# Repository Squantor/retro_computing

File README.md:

# Various retrocomputing projects
This is a collection of retrocomputing projects.
## Structure
* Hardware contains the schematics and PCB's used by the project
* Software contains the software needed for the project, either embedded or PC side software
* CAD contains drawings of casing/mechanisms etc
## Checking out
This project makes extensive use of submodules, use ```git clone --recurse-submodules https://github.com/Squantor/retro_computing.git``` to clone the repository and its submodules in one go.

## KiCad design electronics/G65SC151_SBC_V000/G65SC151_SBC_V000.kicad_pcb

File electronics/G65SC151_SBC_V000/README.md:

# G65SC151 Single Board Computer Version 0
This is a simple test board for the G65SC151 microcontroller chip. Goal is to bring up this chip and getting to know how to program it. Why? I have some retrocomputing projects planned, and I wanted to learn to program the 6502 processor. Instead of going for the standard 6502 with a RAM, ROM and ACIA/UART chip. The G65SC151 has a few facilities built in:
* 64 bytes of RAM
* 27 GPIO pins
* Interval timer
* Some modem communications block
* 6502 style bus interface
This makes it possible to make a working 6502 system with just adding a ROM chip. Neat!
# HSI (Hardware Software Interface)
Still TODO as schematic is still in progress.
## TODO's
Still some things need to be done:
* schematic entry 
* PCB layout
* Review with one night in between
* Produce
* Assemble
* Test & characterise
* update Readme.md with pictures and BOM
## BOM
The G65SC151 is a long obsolete microcontroller using the 6502 processor architecture. Replicating this project you will have to try your luck with a ebay/aliexpress.

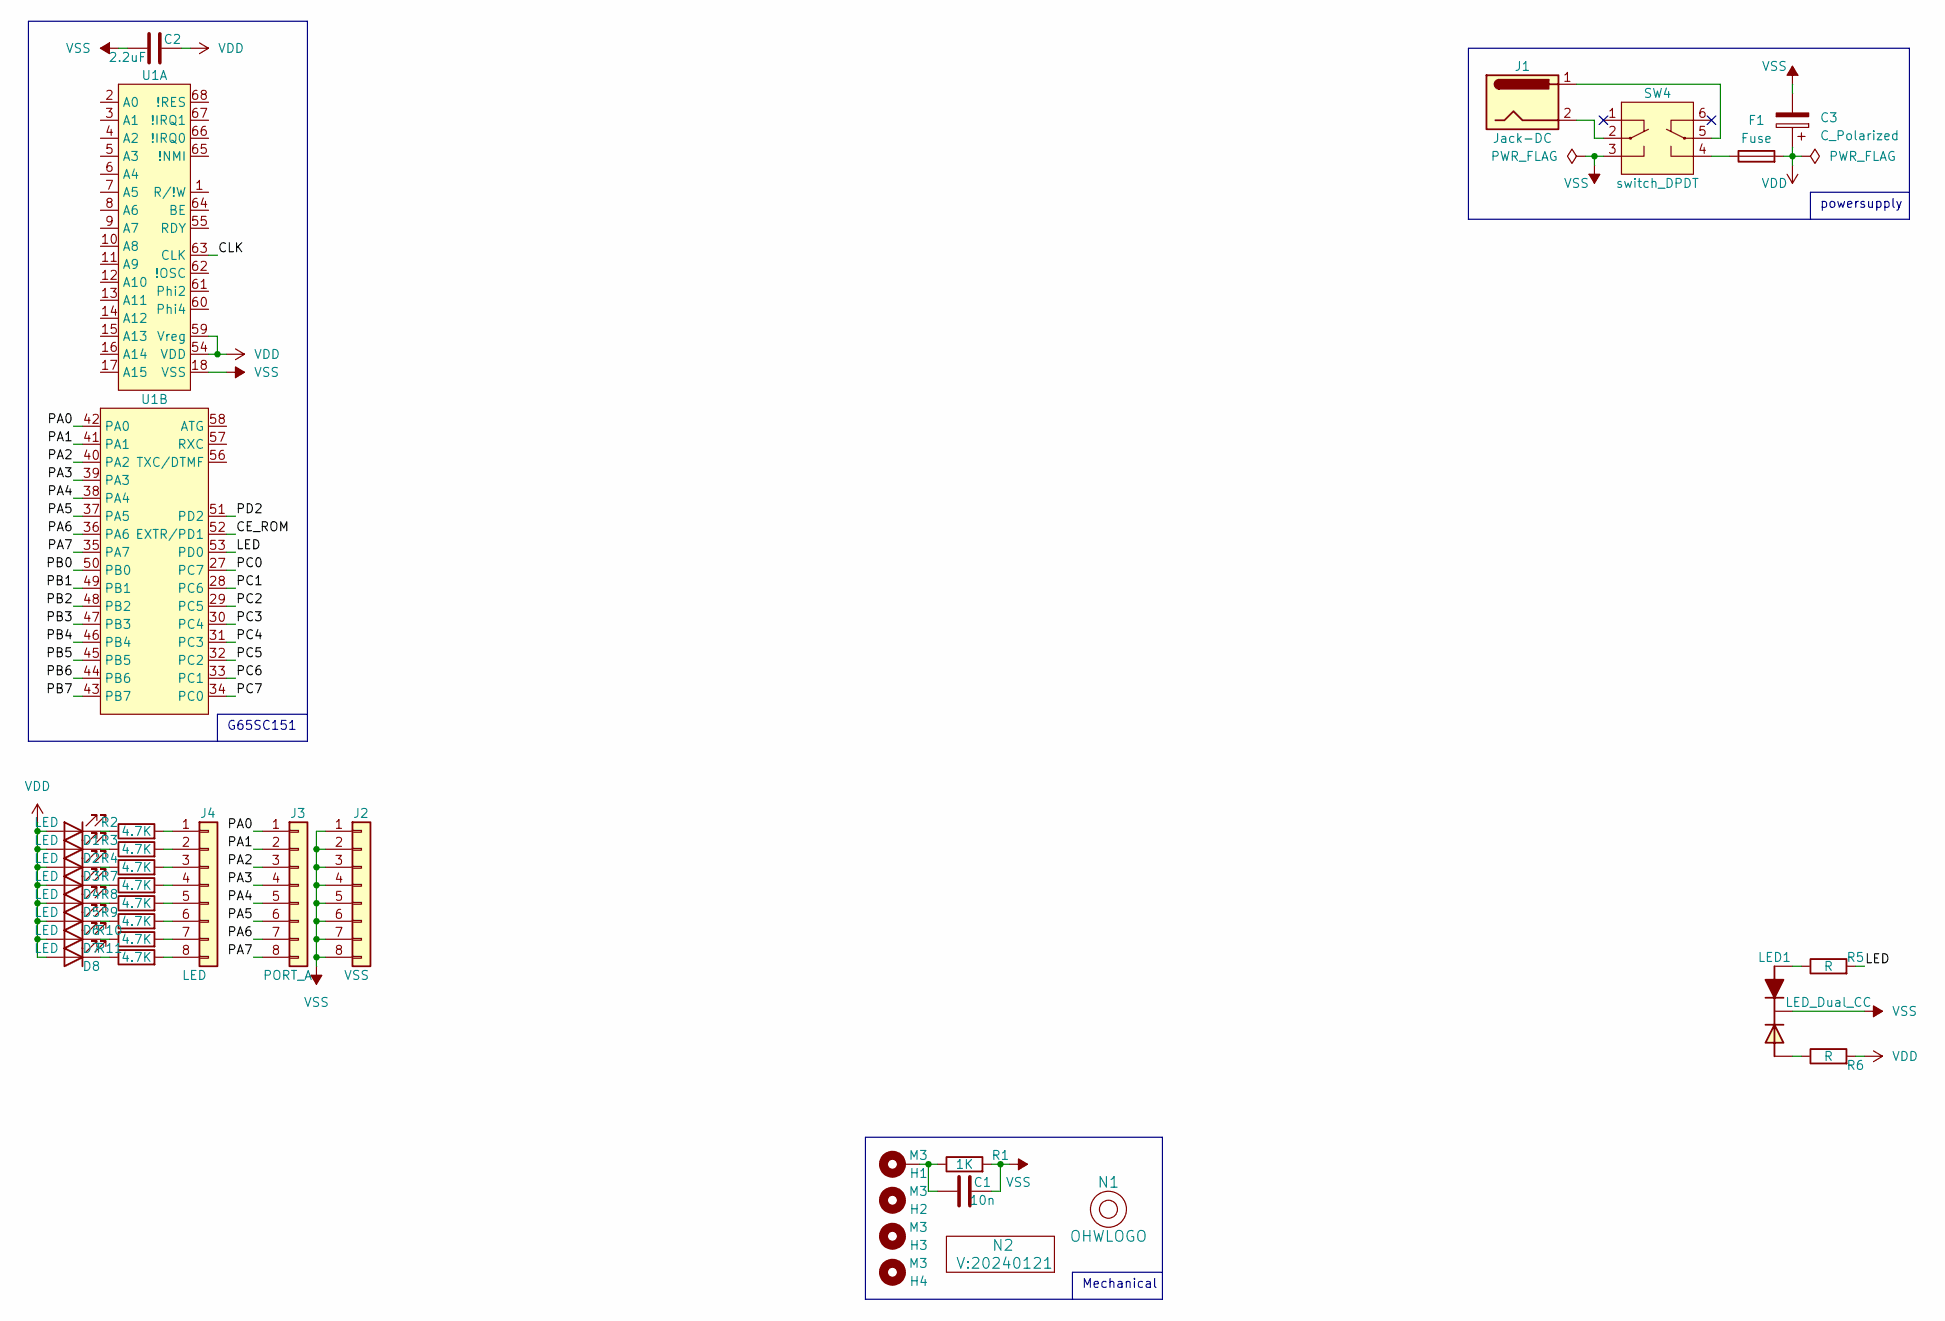
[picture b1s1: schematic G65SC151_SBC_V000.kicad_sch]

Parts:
C1: 10n; C_0805+0603
C2: 2.2uF; C_0805+0603
C3: C_Polarized; C-050-100-elco
D1, D2, D3, D4, D5, D6, D7, D8: LED; LED_0603_hand
F1: Fuse; Fuse_BelFuse_0ZRE0012FF_L8.3mm_W3.8mm
H1, H2, H3, H4: M3; MountingHole_3.2mm_M3_Pad_Via
J1: Jack-DC; BarrelJack_Horizontal_Holed
J2: VSS; Header-0254-1X08-H010
J3: PORT_A; Header-0254-1X08-H010
J4: LED; Header-0254-1X08-H010
LED1: LED_Dual_CC; LED_DUAL_TH245_90deg
N1: OHWLOGO; OSHW-Symbol_6.7x6mm_SilkScreen
N2: V:20240121; Label_Generic
R1: 1K; R_0805+0603
R2, R3, R4, R7, R8, R9, R10, R11: 4.7K; R_0603_hand
R5, R6: R; R_0603_hand
SW4: switch_DPDT; PS-22F02
U1: PLCC-68_THT-Socket

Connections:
/CE_ROM: U1.52 (EXTR/PD1)
/CLK: U1.63 (CLK)
/LED: R5.2, U1.53 (PD0)
/PA0: J3.1, U1.42 (PA0)
/PA1: J3.2, U1.41 (PA1)
/PA2: J3.3, U1.40 (PA2)
/PA3: J3.4, U1.39 (PA3)
/PA4: J3.5, U1.38 (PA4)
/PA5: J3.6, U1.37 (PA5)
/PA6: J3.7, U1.36 (PA6)
/PA7: J3.8, U1.35 (PA7)
/PB0: U1.50 (PB0)
/PB1: U1.49 (PB1)
/PB2: U1.48 (PB2)
/PB3: U1.47 (PB3)
/PB4: U1.46 (PB4)
/PB5: U1.45 (PB5)
/PB6: U1.44 (PB6)
/PB7: U1.43 (PB7)
/PC0: U1.27 (PC7)
/PC1: U1.28 (PC6)
/PC2: U1.29 (PC5)
/PC3: U1.30 (PC4)
/PC4: U1.31 (PC3)
/PC5: U1.32 (PC2)
/PC6: U1.33 (PC1)
/PC7: U1.34 (PC0)
/PD2: U1.51 (PD2)
unnamed: C1.1, H1.1, R1.1
unnamed: D1.1 (K), R2.1
unnamed: D2.1 (K), R3.1
unnamed: D3.1 (K), R4.1
unnamed: D4.1 (K), R7.1
unnamed: D5.1 (K), R8.1
unnamed: D6.1 (K), R9.1
unnamed: D7.1 (K), R10.1
unnamed: D8.1 (K), R11.1
unnamed: F1.1, SW4.4 (SW2_P2)
unnamed: J4.1, R2.2
unnamed: J4.2, R3.2
unnamed: J4.3, R4.2
unnamed: J4.4, R7.2
unnamed: J4.5, R8.2
unnamed: J4.6, R9.2
unnamed: J4.7, R10.2
unnamed: J4.8, R11.2
unnamed: LED1.1 (A1), R5.1
unnamed: LED1.3 (A2), R6.1
unnamed: J1.2, SW4.2 (SW1_C1)
unnamed: J1.1, SW4.5 (SW2_C1)
VDD: C2.2, C3.1, D1.2 (A), D2.2 (A), D3.2 (A), D4.2 (A), D5.2 (A), D6.2 (A), D7.2 (A), D8.2 (A), F1.2, R6.2, U1.54 (VDD), U1.59 (Vreg)
VSS: C1.2, C2.1, C3.2, J2.1, J2.2, J2.3, J2.4, J2.5, J2.6, J2.7, J2.8, LED1.2 (C), R1.2, SW4.3 (SW1_P2), U1.18 (VSS)

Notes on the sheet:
Mechanical
G65SC151
powersupply

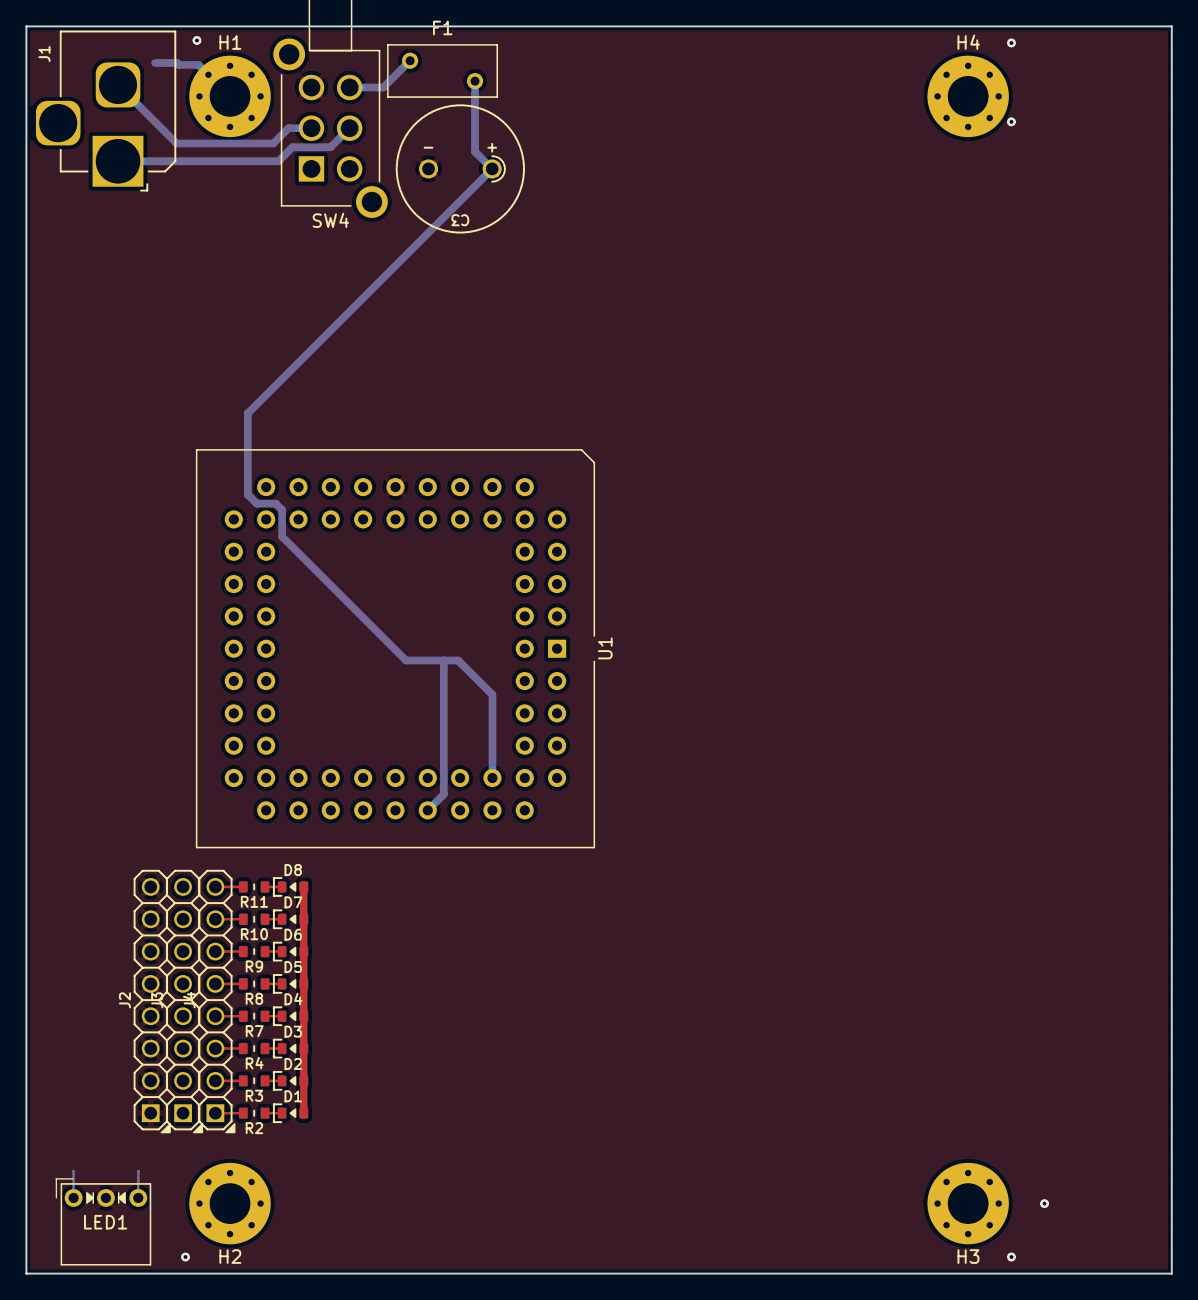
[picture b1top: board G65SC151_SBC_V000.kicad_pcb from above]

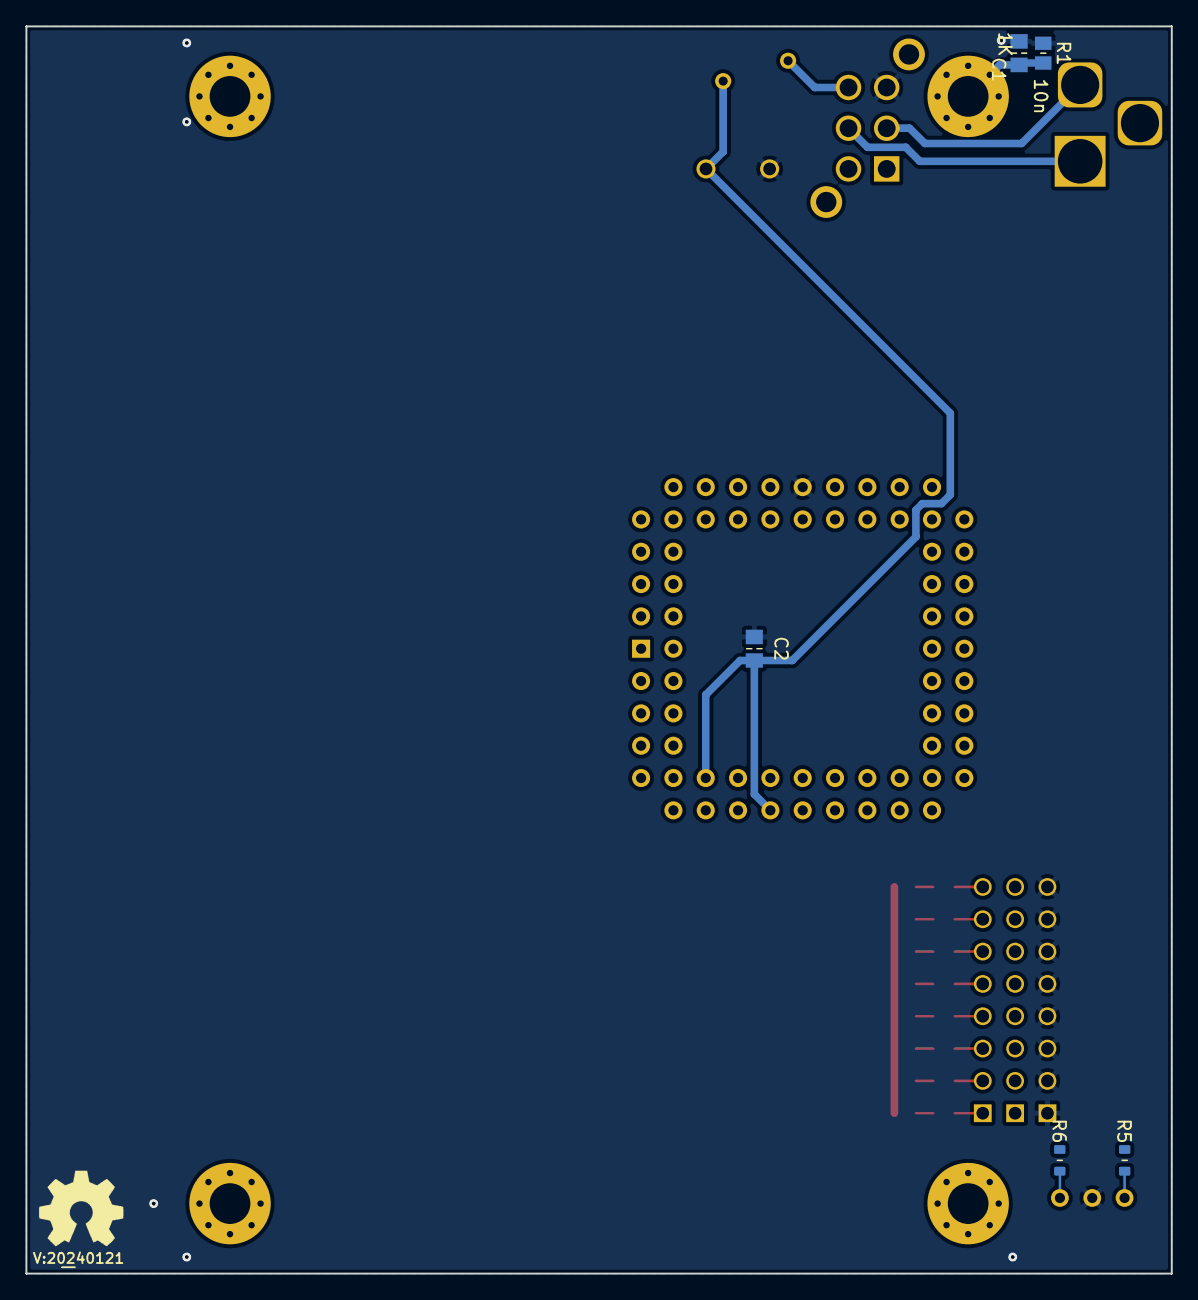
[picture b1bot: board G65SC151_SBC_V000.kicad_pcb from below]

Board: 2 copper layers, 90.0 x 98.0 mm, 36 parts (7 on the bottom side), 33 nets.

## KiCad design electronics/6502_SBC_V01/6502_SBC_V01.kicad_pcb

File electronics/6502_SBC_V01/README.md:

# Tryout 6502 SBC
Simple experiment with a 6502 SBC
# HSI (Hardware Software Interface)
This applies to a project that has a embedded software component. Describe what each pin/bus does, what it is connected to, what its function is and some "safe" behaviour when starting up.
## TODO's
Still some things need to be done:
* schematic entry 
* PCB layout
* Review with one night in between
* Produce
* Assemble
* Test & debug
* update Readme.md with pictures and BOM
## BOM
This is a list of hardware components. If just mentioned a generic component like a 1K 0402 resistor, just name it as such, free to substitute. If you need some special integrated IC's show some sources like Mouser, Digikey, Farnell, or LCSC
* 6502 processor
* 6522 VIA
* 6551 ACIA
## Pictures

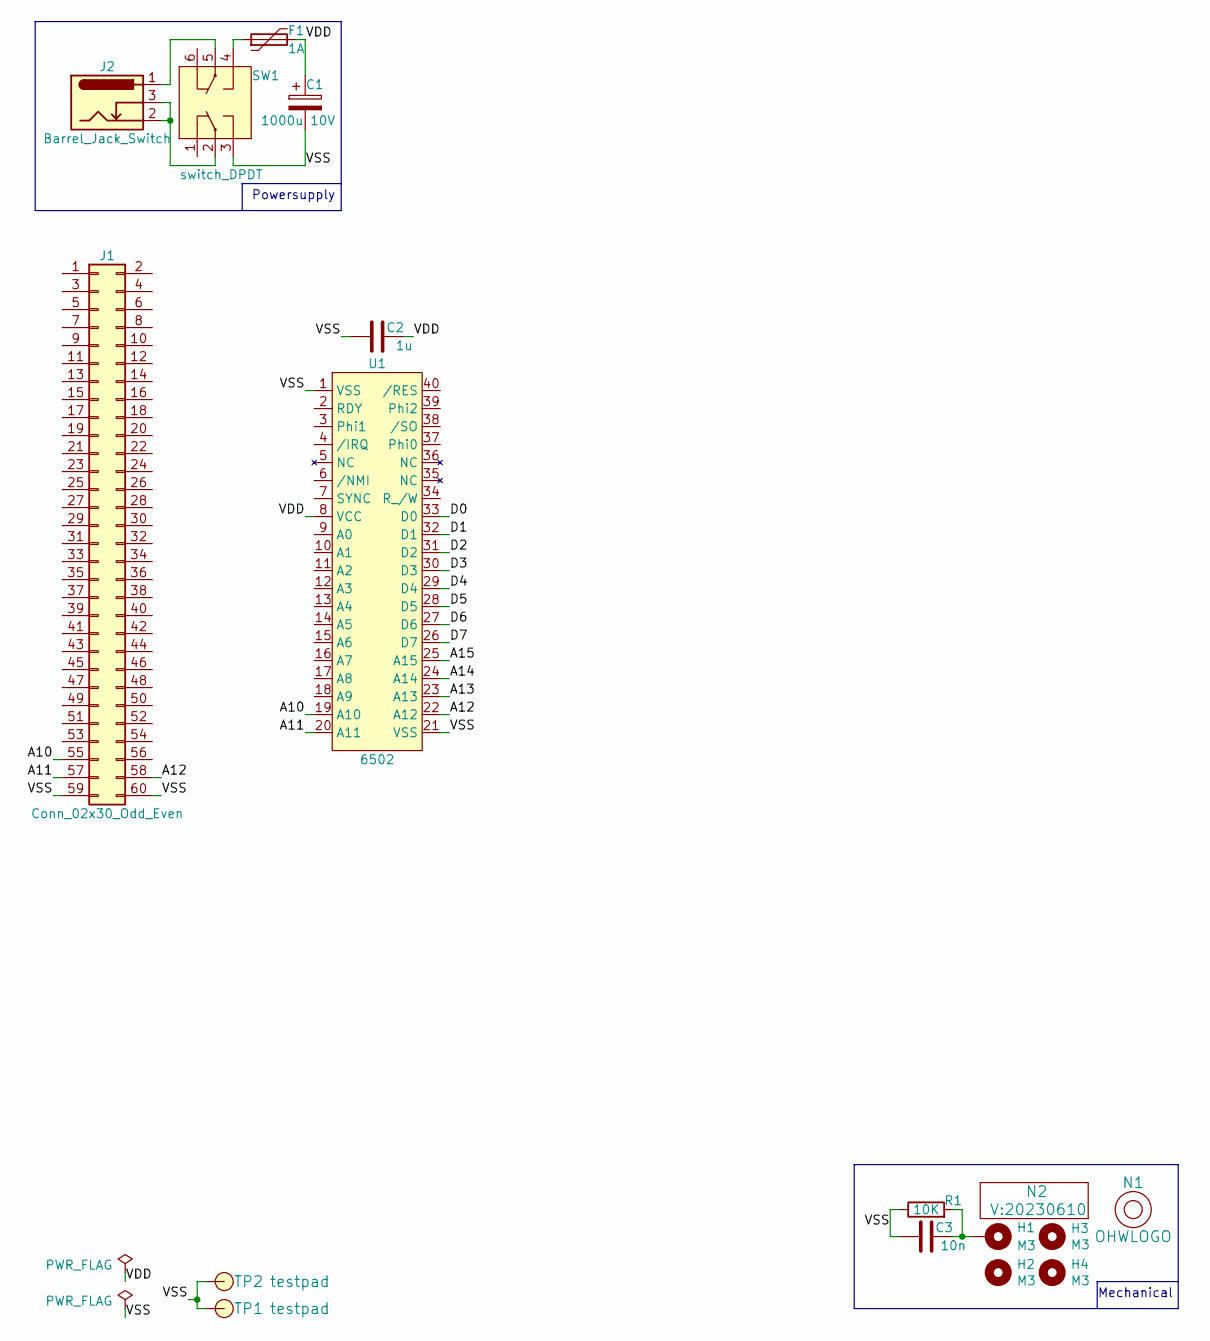
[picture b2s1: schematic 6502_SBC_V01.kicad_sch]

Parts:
C1: 1000u 10V; C-035-100-elco
C2: 1u; C_0805+0603
C3: 10n; C_0805
F1: 1A; Fuse_Bourns_MF-RG1000
H1, H2, H3, H4: M3; MountingHole_3.2mm_M3_Pad_Via
J1: Conn_02x30_Odd_Even; PinHeader_2x30_P2.54mm_Vertical
J2: Barrel_Jack_Switch; BarrelJack_Horizontal_Holed
N1: OHWLOGO; OSHW-Symbol_6.7x6mm_SilkScreen
N2: V:20230610; Label_Generic
R1: 10K; R_0603_hand
SW1: switch_DPDT; PS-22F02
TP1, TP2: testpad; TestPoint_THTPad_D1.0mm_Drill0.5mm
U1: 6502; DIP-40_W15.24mm_Socket_LongPads

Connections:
/A10: J1.55, U1.19 (A10)
/A11: J1.57, U1.20 (A11)
/A12: J1.58, U1.22 (A12)
/A13: U1.23 (A13)
/A14: U1.24 (A14)
/A15: U1.25 (A15)
/D0: U1.33 (D0)
/D1: U1.32 (D1)
/D2: U1.31 (D2)
/D3: U1.30 (D3)
/D4: U1.29 (D4)
/D5: U1.28 (D5)
/D6: U1.27 (D6)
/D7: U1.26 (D7)
/VDD: C1.1, C2.2, F1.2, U1.8 (VCC)
/VSS: C1.2, C2.1, C3.1, J1.59, J1.60, R1.1, SW1.3 (SW1_P2), TP1.1, TP2.1, U1.1 (VSS), U1.21 (VSS)
unnamed: F1.1, SW1.4 (SW2_P2)
unnamed: C3.2, H1.1, R1.2
unnamed: J2.1, SW1.5 (SW2_C1)
unnamed: J2.2, J2.3, SW1.2 (SW1_C1)

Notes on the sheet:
Mechanical
Powersupply

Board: 2 copper layers, 17 parts (0 on the bottom side), 9 nets, no tracks yet.

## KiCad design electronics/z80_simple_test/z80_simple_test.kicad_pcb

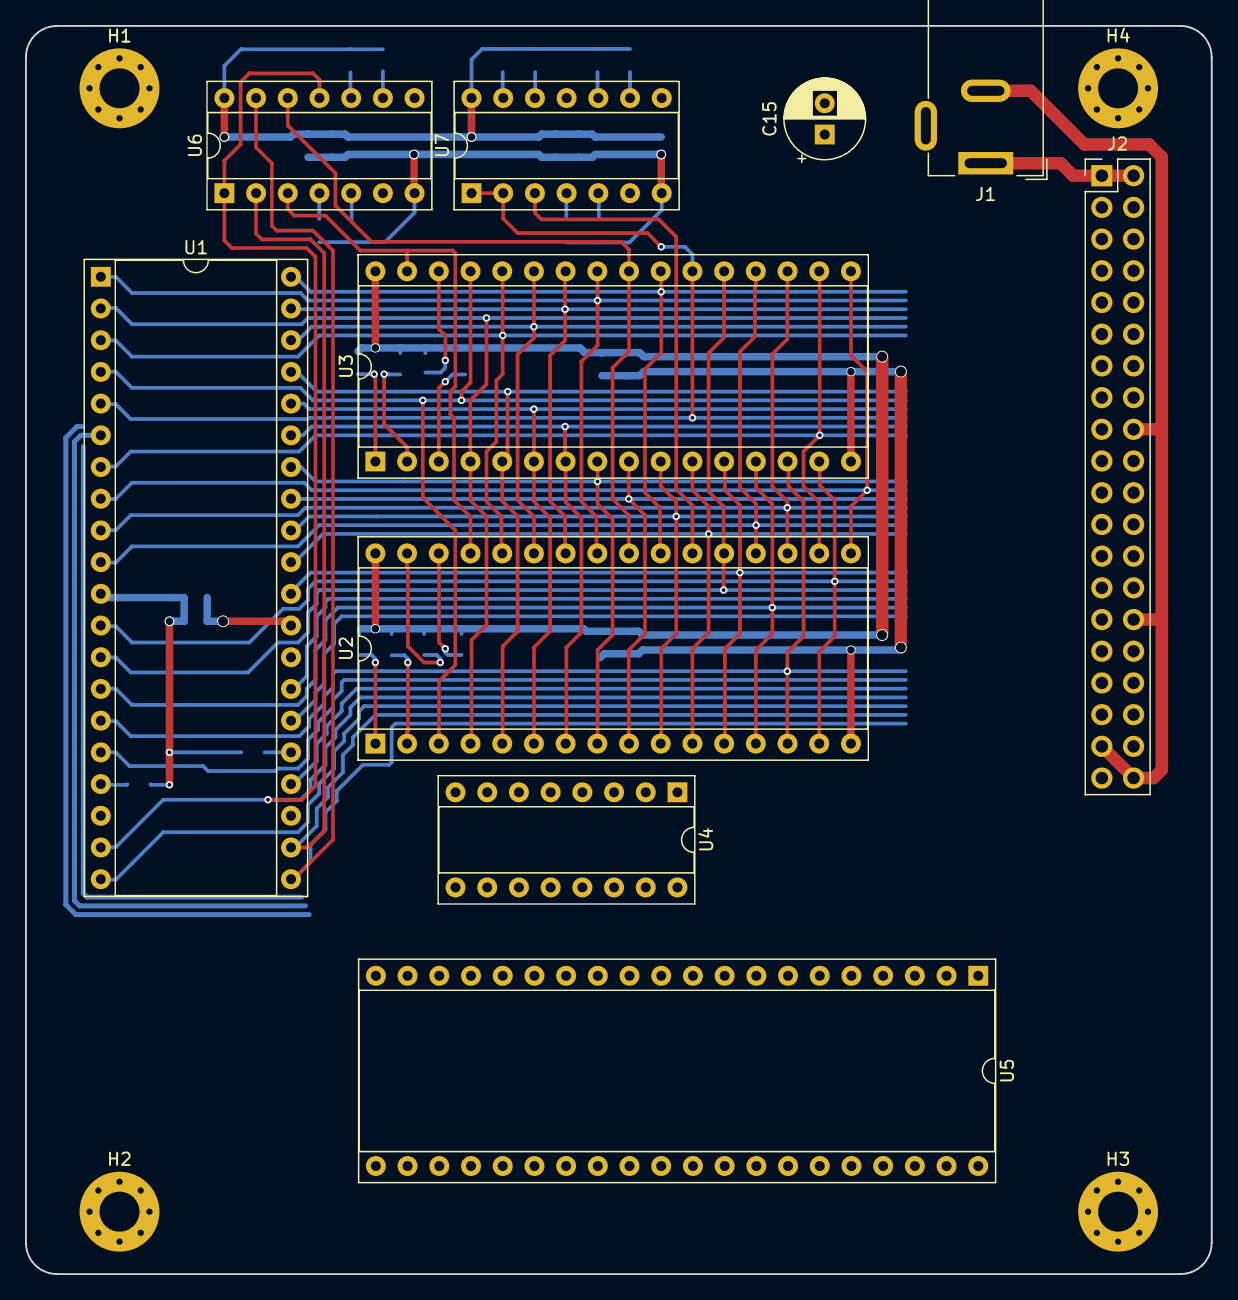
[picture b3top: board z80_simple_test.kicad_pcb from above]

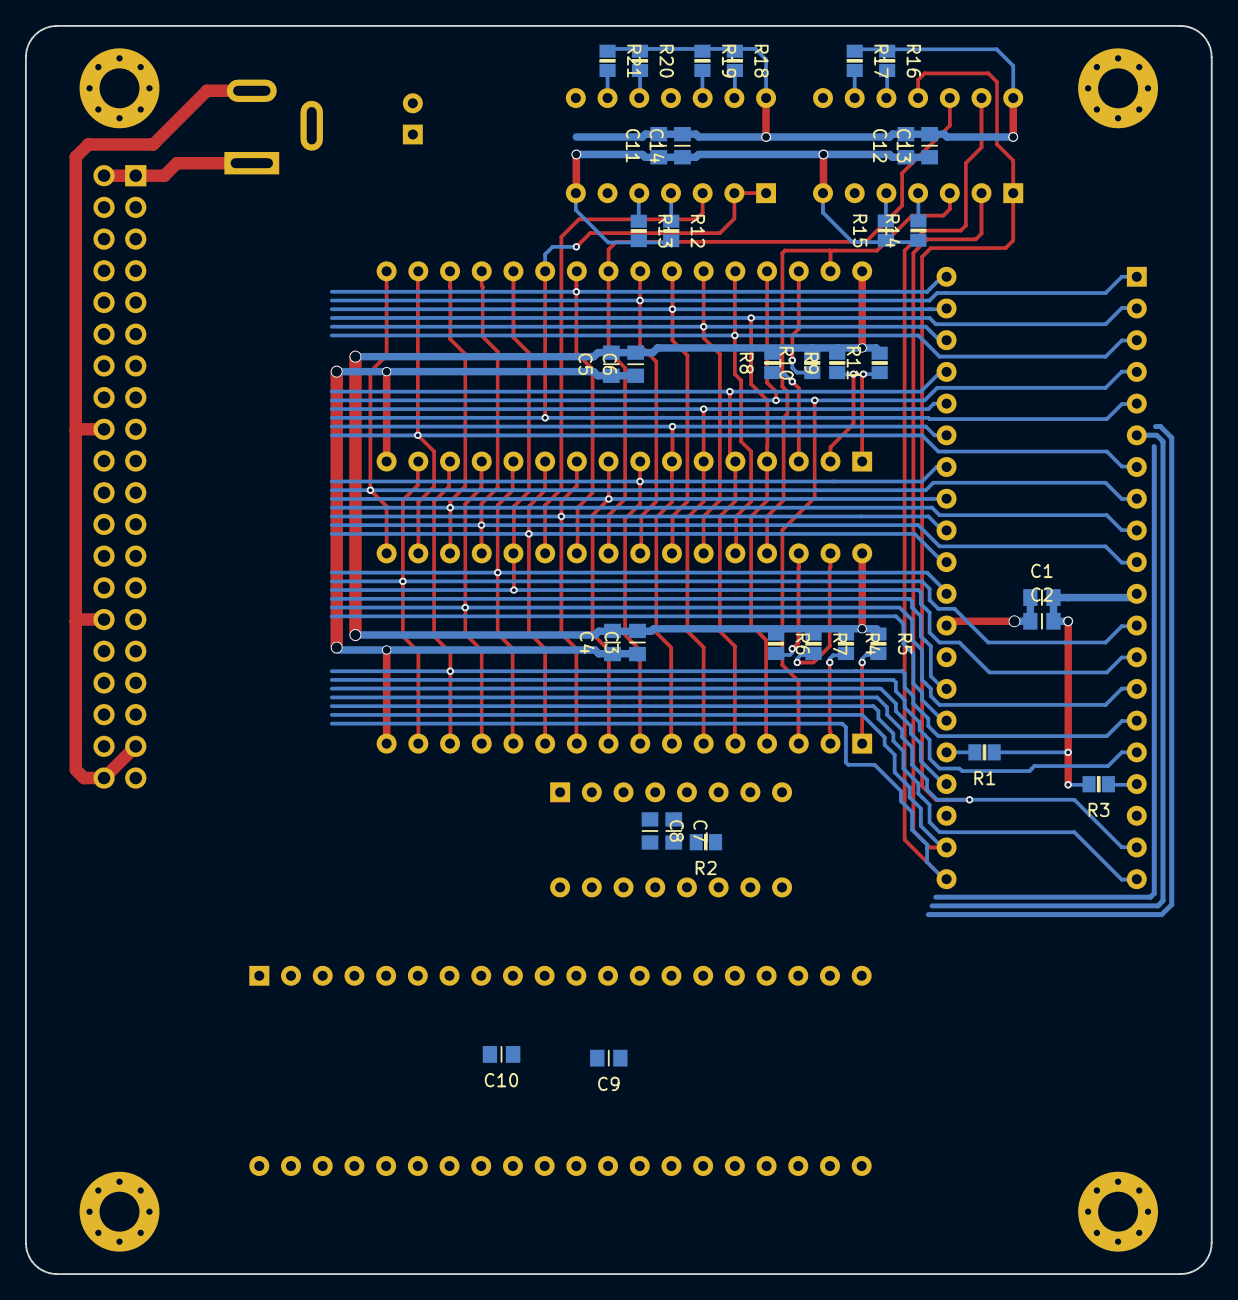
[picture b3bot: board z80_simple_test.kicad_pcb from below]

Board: 2 copper layers, 95.0 x 100.0 mm, 51 parts (35 on the bottom side), 61 nets.

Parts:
C1, C3, C5, C8, C9, C13, C14: 100n; C_0805+0603
C2, C4, C6, C7, C10, C11, C12: 1u; C_0805+0603
C15: CP; CP_Radial_D6.3mm_P2.50mm
H1, H2, H3, H4: M3; MountingHole_3.2mm_M3_Pad_Via
J1: Barrel_Jack_Switch; BarrelJack_Wuerth_6941xx301002
J2: Conn_02x15_Odd_Even; PinHeader_2x20_P2.54mm_Vertical
N1: OHWLOGO; OSHW-Symbol_6.7x6mm_SilkScreen
N2: V:20191023; Label_Generic
R1, R2, R3, R4, R5, R6, R7, R8, R9, R10, R11, R12, R13, R14, R15, R16, R17, R18, R19, R20, R21: 10k; R_0805+0603
U1: Z84C000XPEG; DIP-40_W15.24mm_Socket
U2: SRAM_512K8B_DIP_SOP_SOJ; DIP-32_W15.24mm_Socket
U3: EEPROM_512K8B_DIP; DIP-32_W15.24mm_Socket
U4: 74XX138; DIP-16_W7.62mm_Socket
U5: Z84C40XPEG; DIP-40_W15.24mm_Socket
U6: 74XX32; DIP-14_W7.62mm_Socket
U7: 74XX00; DIP-14_W7.62mm_Socket

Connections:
/!IEI: J2.27, U5.6
/!INT: J2.31, U1.16, U5.5
/!IORQ: J2.35, U1.20, U4.4, U5.36
/!M1: J2.29, U1.27, U5.8
/!MEM_RD: U2.24, U3.24, U6.12
/!MEM_WR: U2.29, U3.31, U6.3
/!MREQ: J2.34, U1.19, U6.1, U6.11
/!NMI: R3.1, U1.17
/!RAM_CE: U2.22, U7.3
/!RD: J2.38, U1.21, U5.32, U6.13
/!RESET: J2.32, U1.26, U5.21
/!WAIT: J2.33, U1.24
/!WR: J2.36, U1.22, U6.2
/A0: J2.20, U1.30, U2.12, U3.12, U5.34
/A1: J2.17, U1.31, U2.11, U3.11, U5.33
/A2: J2.15, U1.32, U2.10, U3.10, U4.1
/A3: J2.16, U1.33, U2.9, U3.9, U4.2
/A4: J2.13, U1.34, U2.8, U3.8, U4.3
/A5: J2.14, U1.35, U2.7, U3.7, U4.5
/A6: J2.11, U1.36, U2.6, U3.6
/A7: J2.12, U1.37, U2.5, U3.5
/A8: J2.9, U1.38, U2.27, U3.27
/A9: J2.10, U1.39, U2.26, U3.26
/A10: J2.7, U1.40, U2.23, U3.23
/A11: J2.8, U1.1, U2.25, U3.25
/A12: J2.5, U1.2, U2.4, U3.4
/A13: J2.6, U1.3, U2.28, U3.28
/A14: J2.3, U1.4, U2.3, U3.29
/A15: J2.4, U1.5, U3.22, U7.1, U7.2
/A15_RAM: R7.2, U2.31
/A15_ROM: R8.1, U3.3
/A16_RAM: R4.2, U2.2
/A16_ROM: R9.1, U3.2
/A17_RAM: R5.2, U2.1
/A17_ROM: R10.1, U3.30
/A18_RAM: R6.2, U2.30
/A18_ROM: R11.1, U3.1
/D0: J2.28, U1.14, U2.13, U3.13, U5.40
/D1: J2.25, U1.15, U2.14, U3.14, U5.1
/D2: J2.26, U1.12, U2.15, U3.15, U5.39
/D3: J2.23, U1.8, U2.17, U3.17, U5.2
/D4: J2.24, U1.7, U2.18, U3.18, U5.38
/D5: J2.21, U1.9, U2.19, U3.19, U5.3
/D6: J2.22, U1.10, U2.20, U3.20, U5.37
/D7: J2.19, U1.13, U2.21, U3.21, U5.4
/MCLK: J2.39, U1.6, U5.20
/SEL_SIO: U4.14, U5.35
/VDD: C1.2, C2.2, C3.2, C4.2, C5.2, C6.2, C7.2, C8.2, C9.2, C10.2, C11.2, C12.2, C13.2, C14.2, C15.1, J1.1, J2.1, J2.2, R1.1, R2.2, R3.2, R4.1, R5.1, R6.1, R7.1, R8.2, R9.2, R10.2, R11.2, R16.1, R17.1, R18.1, R19.1, R20.1, R21.1, U1.11, U2.32, U3.32, U4.16, U5.9, U6.14, U7.14
/VSS: C1.1, C2.1, C3.1, C4.1, C5.1, C6.1, C7.1, C8.1, C9.1, C10.1, C11.1, C12.1, C13.1, C14.1, C15.2, J1.2, J2.18, J2.30, J2.37, J2.40, R12.2, R13.2, R14.1, R15.1, U1.29, U2.16, U3.16, U4.8, U5.31, U7.7
unnamed: R1.2, U1.25
unnamed: R2.1, U4.6
unnamed: R12.1, U7.4
unnamed: R13.1, U7.5
unnamed: R14.2, U6.4
unnamed: R15.2, U6.5
unnamed: R16.2, U6.10
unnamed: R17.2, U6.9
unnamed: R18.2, U7.13
unnamed: R19.2, U7.12
unnamed: R20.2, U7.10
unnamed: R21.2, U7.9

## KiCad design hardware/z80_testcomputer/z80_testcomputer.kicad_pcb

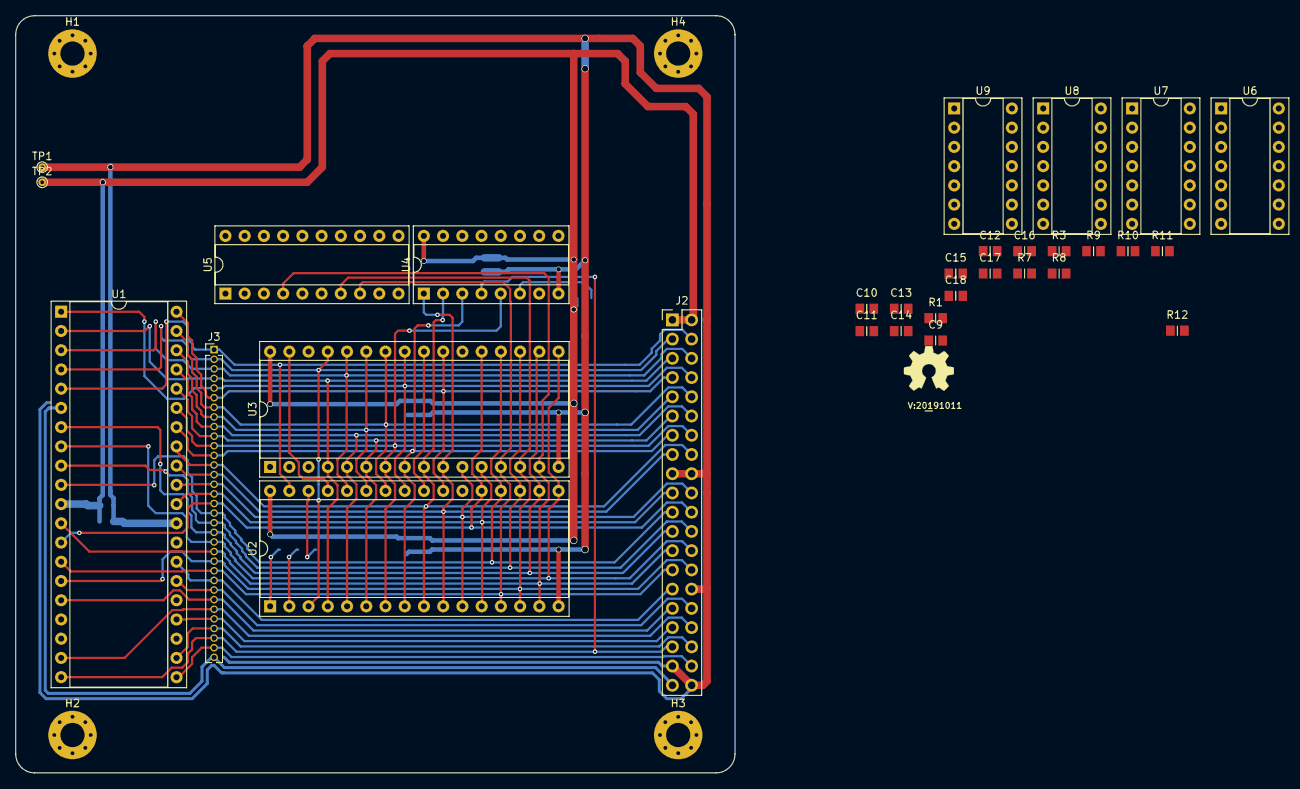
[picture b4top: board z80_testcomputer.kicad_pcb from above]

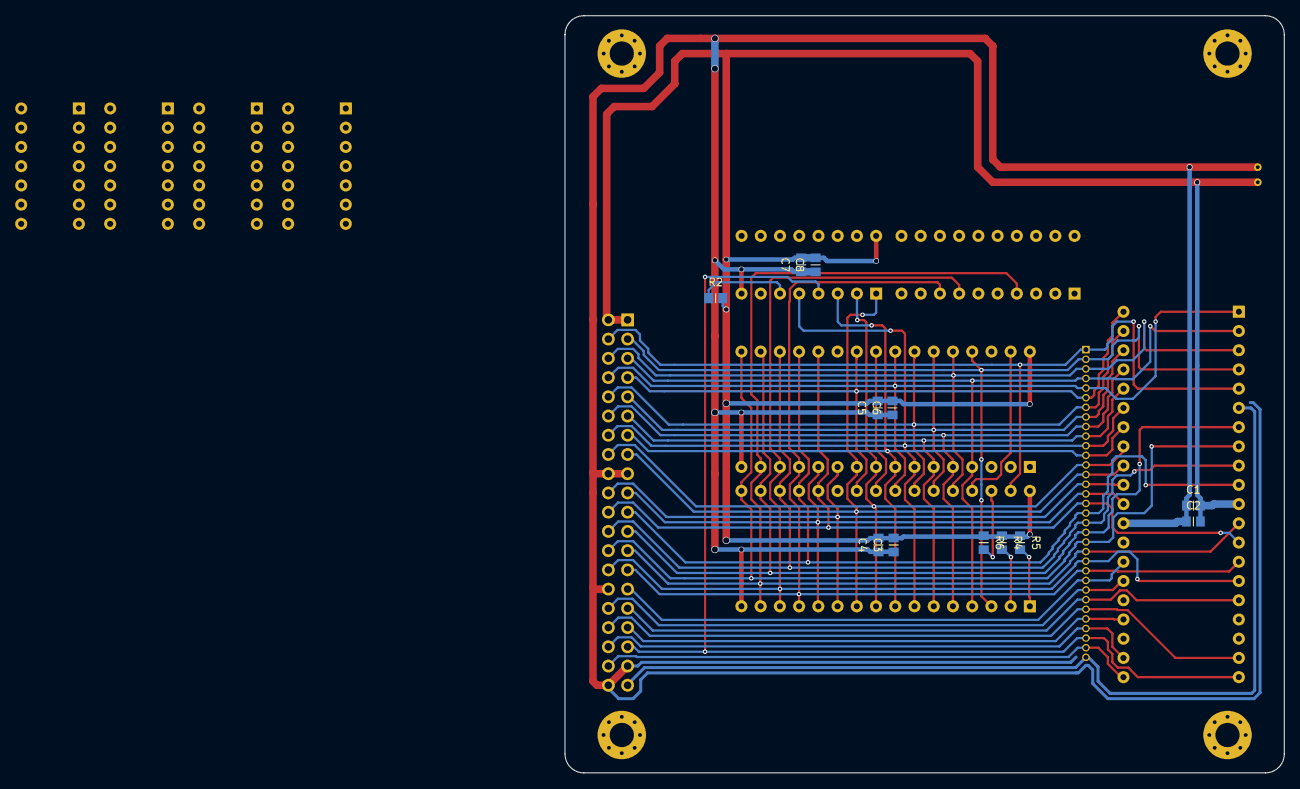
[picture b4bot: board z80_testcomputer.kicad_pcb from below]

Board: 2 copper layers, 95.0 x 100.0 mm, 49 parts (12 on the bottom side), 69 nets.

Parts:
C1, C3, C5, C8, C9, C11, C13, C15, C17: 100n; C_0805+0603
C2, C4, C6, C7, C10, C12, C14, C16, C18: 1u; C_0805+0603
H1, H2, H3, H4: M3; MountingHole_3.2mm_M3_Pad_Via
J2: Conn_02x15_Odd_Even; PinHeader_2x20_P2.54mm_Vertical
J3: Conn_01x32; PinHeader_1x33_P1.27mm_Vertical
N1: OHWLOGO; OSHW-Symbol_6.7x6mm_SilkScreen
N2: V:20191011; Label_Generic
R1, R2, R3, R4, R5, R6, R7, R8, R9, R10, R11, R12: 10k; C_0805+0603
TP1, TP2: testpad; TestPoint_THTPad_D1.0mm_Drill0.5mm
U1: Z84C000XPEG; DIP-40_W15.24mm_Socket
U2: SRAM_512K8B_DIP_SOP_SOJ; DIP-32_W15.24mm_Socket
U3: EEPROM_512K8B_DIP; DIP-32_W15.24mm_Socket
U4: 74XX138; DIP-16_W7.62mm_Socket
U5: 74XX273; DIP-20_W7.62mm_Socket
U6, U8: 74XX32; DIP-14_W7.62mm_Socket
U7, U9: 74XX00; DIP-14_W7.62mm_Socket

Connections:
/!BOOT: U5.9, U8.4
/!HI4K: U7.1, U7.13, U9.8
/!INT: J2.31, J3.27, U1.16
/!IORQ: J2.35, J3.31, U1.20, U4.4, U6.12
/!IOSEL0: U4.15, U6.9
/!IO_WR: U6.10, U6.11
/!LOW4K: U7.2, U7.12, U8.11
/!M1: J2.29, J3.25, U1.27
/!MEM_RD: U2.24, U3.24, U6.3
/!MEM_WR: U2.29, U3.31, U6.6
/!MREQ: J2.34, J3.28, U1.19, U6.2, U6.4
/!NMI: R3.1, U1.17
/!RAM_CE: U2.22, U7.3
/!RD: J2.38, J3.32, U1.21, U6.1
/!RESET: J2.32, J3.26, U1.26, U5.1
/!ROM_CE: U3.22, U7.8
/!WAIT: J2.33, J3.29, U1.24
/!WR: J2.36, J3.30, U1.22, U6.5, U6.13
/A0: J2.19, J3.16, U1.30, U2.12, U3.12
/A1: J2.20, J3.15, U1.31, U2.11, U3.11
/A2: J2.15, J3.14, U1.32, U2.10, U3.10, U4.1
/A3: J2.16, J3.13, U1.33, U2.9, U3.9, U4.2
/A4: J2.13, J3.12, U1.34, U2.8, U3.8, U4.3
/A5: J2.14, J3.11, U1.35, U2.7, U3.7, U4.5
/A6: J2.11, J3.10, U1.36, U2.6, U3.6
/A7: J2.12, J3.9, U1.37, U2.5, U3.5
/A8: J2.9, J3.8, U1.38, U2.27, U3.27
/A9: J2.10, J3.7, U1.39, U2.26, U3.26
/A10: J2.7, J3.6, U1.40, U2.23, U3.23
/A11: J2.8, J3.5, U1.1, U2.25, U3.25
/A12: J2.5, J3.4, U1.2, U2.4
/A12_ROM: U3.4, U5.6
/A13: J2.6, J3.3, U1.3, U2.28, U8.5, U9.9
/A13_ROM: U3.28, U5.5
/A14: J2.3, J3.2, U1.4, U2.3, U8.2, U9.2
/A14_ROM: U3.29, U5.2
/A15: J2.4, J3.1, U1.5, U2.31, U8.1, U9.1
/A15_ROM: U3.3, U5.19
/A16_RAM: R4.2, U2.2
/A16_ROM: U3.2, U5.16
/A17_RAM: R5.2, U2.1
/A17_ROM: U3.30, U5.15
/A18_RAM: R6.2, U2.30
/A18_ROM: U3.1, U5.12
/BANK_CP: U5.11, U6.8
/D0: J2.27, J3.24, U1.14, U2.13, U3.13, U5.8
/D1: J2.28, J3.23, U1.15, U2.14, U3.14, U5.7
/D2: J2.25, J3.22, U1.12, U2.15, U3.15, U5.4
/D3: J2.26, J3.21, U1.8, U2.17, U3.17, U5.3
/D4: J2.23, J3.20, U1.7, U2.18, U3.18, U5.18
/D5: J2.24, J3.19, U1.9, U2.19, U3.19, U5.17
/D6: J2.21, J3.18, U1.10, U2.20, U3.20, U5.14
/D7: J2.22, J3.17, U1.13, U2.21, U3.21, U5.13
/MCLK: J2.39, J3.33, U1.6
/VDD: C1.2, C2.2, C3.2, C4.2, C5.2, C6.2, C7.2, C8.2, C9.2, C10.2, C11.2, C12.2, C13.2, C14.2, C15.2, C16.2, C17.2, C18.2, J2.1, J2.2, R1.1, R2.2, R3.2, R4.1, R5.1, R6.1, R7.1, R8.1, R9.1, R10.1, R11.1, R12.1, TP2.1, U1.11, U2.32, U3.32, U4.16, U5.20, U6.14, U7.14, U8.14, U9.14
/VSS: C1.1, C2.1, C3.1, C4.1, C5.1, C6.1, C7.1, C8.1, C9.1, C10.1, C11.1, C12.1, C13.1, C14.1, C15.1, C16.1, C17.1, C18.1, J2.17, J2.18, J2.30, J2.37, J2.40, TP1.1, U1.29, U2.16, U3.16, U4.8, U5.10, U6.7, U7.7, U8.7, U9.7
unnamed: R1.2, U1.25
unnamed: R2.1, U4.6
unnamed: R7.2, U7.4
unnamed: R8.2, U7.5
unnamed: R9.2, U9.4
unnamed: R10.2, U9.5
unnamed: R11.2, U8.10
unnamed: R12.2, U8.9
unnamed: U7.9, U7.10, U7.11
unnamed: U8.6, U8.12
unnamed: U8.3, U8.13
unnamed: U9.10, U9.11
unnamed: U9.3, U9.12, U9.13

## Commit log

2018-01-20 * added intel PCI development backplane documentation
2018-01-20 * added PCI specification * added two xilinx application notes for 5V tolerance and a possible solution
2019-10-11 updated project landing readme
2019-10-11 added kicad git ignores
2019-10-11 added pcb library
2019-10-11 inital addition of simple Z80 test computer
2019-10-12 changed mounting holes
2019-10-13 added bus
2019-10-13 updated pcb library due to zilog library
2019-10-13 added zilog library
2019-10-13 added z80 cpu, modified interface bus pinning
2019-10-13 added decoupling for Z80 CPU
2019-10-13 first bus connections
2019-10-13 some bus routing, lets add a RAM/ROM
2019-10-13 experimenting with SRAM placement, PDIP is too big, need to switch to PLCC memories/processor
2019-10-14 additional package changes
2019-10-14 added EEPROMS
2019-10-14 added EEPROM, experimenting with packages
2019-10-14 updated zilog device
2019-10-14 again switched back to PDIP to make a simpler board and easier to route
2019-10-15 added bus testpoints for new layout test
2019-10-15 changed pcb rules a bit, added a net class for clock, layed out bus, RAM/ROM combo and added enables
2019-10-15 further layout of RAM/ROM, bus seems good enough
2019-10-15 some power distribution routing
2019-10-15 further power and bus routing
2019-10-15 further bus routing, made an error, need to shift a ton of lines
2019-10-16 changed address bus ordering, changed peripheral bus to something smaller
2019-10-16 expansion bus changes to make it easier to layout, routed mainboard busses completely
2019-10-16 started routing PIO chip
2019-10-17 clock rerouted, removed PIO chip
2019-10-17 some repartitioning
2019-10-17 updating with some logic chips
2019-10-17 added IO space decoder
2019-10-17 wrong package for 74138, placement on PCB
2019-10-17 routed IO logic
2019-10-17 minor updates
2019-10-17 updated I/O selection logic to disable at higher address
2019-10-18 added 74XX273
2019-10-18 fixed incorrect schematic symbol library
2019-10-18 initial start on banking logic
2019-10-18 updated library to include quad OR gates
2019-10-18 finished banking logic
2019-10-18 updated library, fixed some ERC errors, terminated unused pins
2019-10-19 added a bunch of addressing logic
2019-10-19 starting placing some parts
2019-10-19 changed banking bit ordering again to ease routing, rerouted part of I/O selection logic
2019-10-19 routed banking circuit, placing address select logic
2019-10-19 added even simpler z80 computer project
2019-10-19 relayout of busses, more compactified, added two PIO's to check space for SIO
2019-10-19 minor layout changes
2019-10-20 ripped up full bus, now experimenting with different ordering
2019-10-20 z84C00 layout side completed, routing bus underneath memory chips
2019-10-20 further layout
2019-10-21 after a bunch of false starts, this bus setup seems workable
2019-10-21 newer pcb library
2019-10-21 added zilog SIO to schematic and PCB
2019-10-22 routed bus under memory chips
2019-10-23 added memory select logic, updated versionnumber
2019-10-23 added barreljack powersupply
2019-10-23 added address selection logic
2019-10-23 added barreljack to PCB
2019-10-23 selection logic placement
2019-10-24 futher layout of the mainboard bus, replaced footprints of resistors with a bit more compact 0805/0603 universal footprint
2019-10-24 library reorganisation
2019-10-24 added power switch, need to rethink layout (again)
2019-12-25 further routing
2019-12-25 added capacitor and removed power switch, it is just a test
2019-12-25 started placement of SIO
2019-12-25 SIO placement
2023-06-10 moving to more logical name
2023-06-10 updated to newest PCB library
2023-06-10 changed submodule url and updated submodule
2023-06-10 changed submodule URL
2023-06-10 moved kicad gitignored
2023-06-10 started with 6502 simple SBC
2024-01-21 updated PCB library
2024-01-21 started with the G65SC151 SBC Version 0
2024-01-22 ignoring kicad 7 temporaries
2024-01-22 WIP schematic and PCB
